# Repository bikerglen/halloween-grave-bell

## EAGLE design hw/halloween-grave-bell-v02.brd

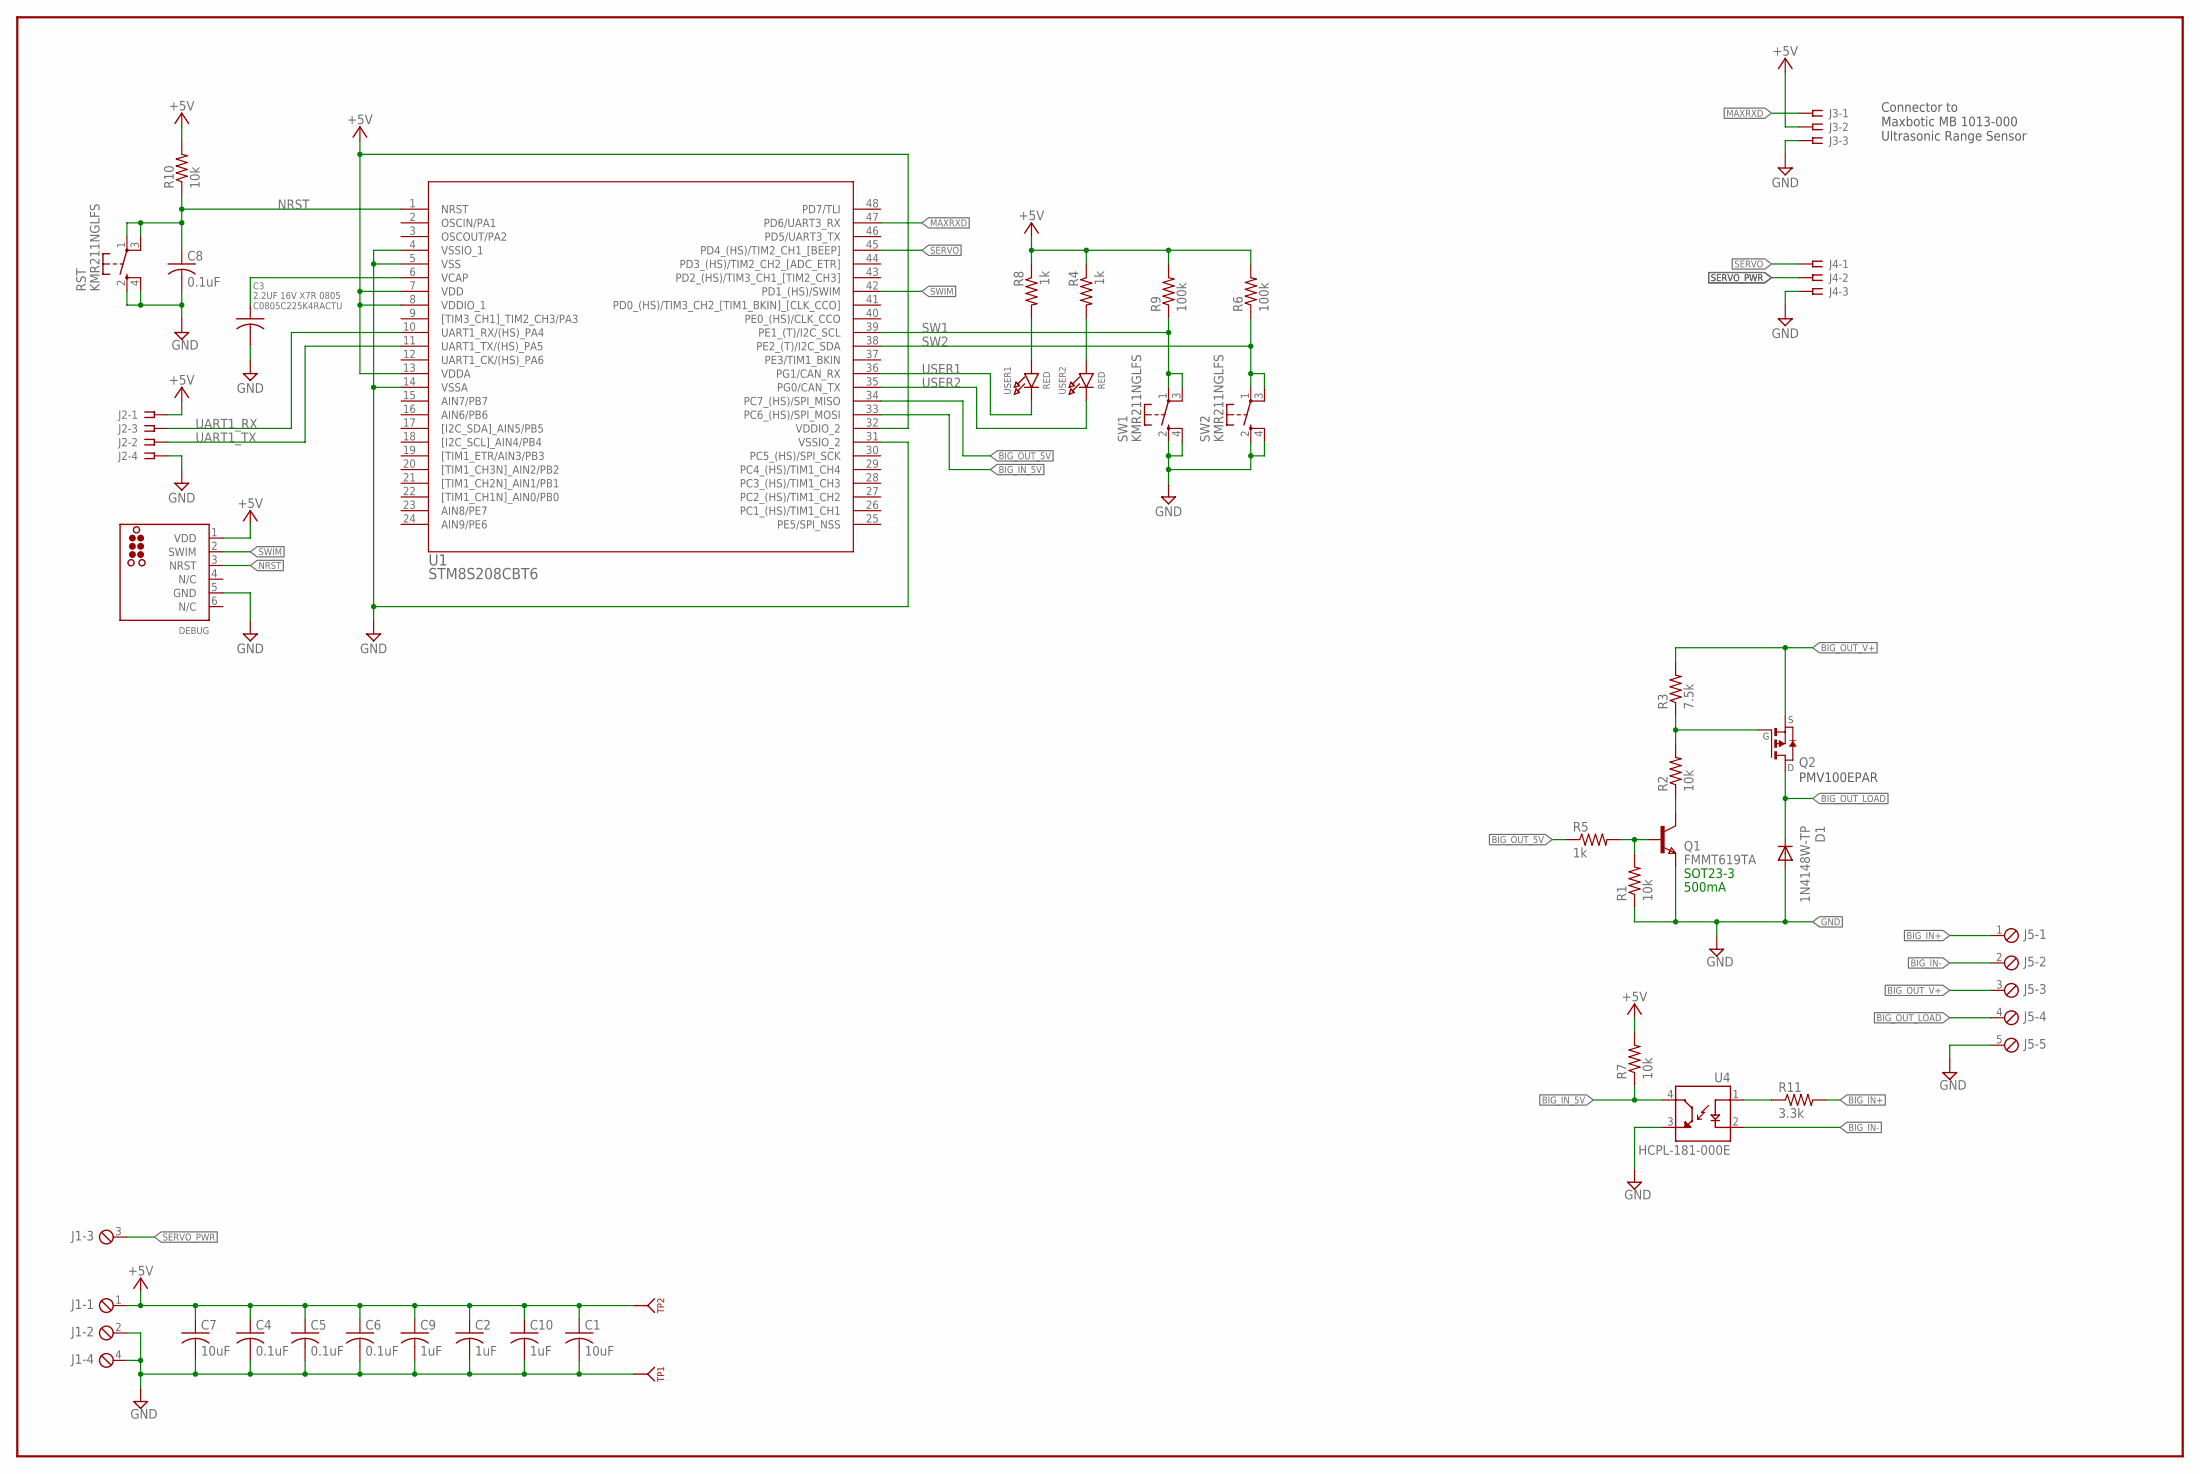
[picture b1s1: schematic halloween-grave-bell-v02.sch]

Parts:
C1, C7: 10uF; C1210; MFR_PART_NO C1210C105K4PACTU
C2, C9, C10: 1uF; C0603
C3: 2.2UF 16V X7R 0805; C0805; MFR_PART_NUM C0805C225K4RACTU
C4, C5, C6: 0.1uF; C0603
C8: 0.1uF; C0805
D1: 1N4148W-TP; SOD123
DEBUG: TC2030-NL-STM8; TC2030-NL
J1: MPT4; 4POL254
J2: SSW-104-02-S-S
J3, J4: SSW-103-02-S-S
J5: MPT5; 5POL254
Q1: FMMT619TA; SOT-23
Q2: PMOSSOT23; SOT-23
R1, R2, R7: 10k; R0603
R3: 7.5k; R0603
R4, R8: 1k; R0805
R5: 1k; R0603
R6, R9: 100k; R0805
R10: 10k; R0805
R11: 3.3k; R0603
RST: KMR211NGLFS; KMR2
SW1, SW2: KMR211NGLFS; KMR2
TP1, TP2: KEYSTONE_500X; KEYSTONE_TP500X
U1: STM8S208CBT6; LQFP-48_STM
U4: HCPL-181-000E; SOIC254P675X240-4N
USER1, USER2: RED; CHIPLED_0805_NOOUTLINE

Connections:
+5V: C1.1, C2.1, C4.1, C5.1, C6.1, C7.1, C9.1, C10.1, DEBUG.1 (VDD), J1.1, J2.1, J3.2, R4.1, R6.2, R7.2, R8.1, R9.2, R10.2, TP2.1, U1.7 (VDD), U1.8 (VDDIO_1), U1.13 (VDDA), U1.32 (VDDIO_2)
BIG_IN+: J5.1, R11.2
BIG_IN-: J5.2, U4.2 (CATHODE)
BIG_IN_5V: R7.1, U1.33 (PC6_(HS)/SPI_MOSI), U4.4 (COLLECTOR)
BIG_OUT_5V: R5.1, U1.34 (PC7_(HS)/SPI_MISO)
BIG_OUT_LOAD: D1.C, J5.4, Q2.1 (D)
BIG_OUT_V+: J5.3, Q2.2 (S), R3.2
GND: C1.2, C2.2, C3.2, C4.2, C5.2, C6.2, C7.2, C8.2, C9.2, C10.2, D1.A, DEBUG.5 (GND), J1.2, J1.4, J2.4, J3.3, J4.3, J5.5, Q1.2 (E), R1.1, RST.2 (S), RST.4 (S1), SW1.2 (S), SW1.4 (S1), SW2.2 (S), SW2.4 (S1), TP1.1, U1.4 (VSSIO_1), U1.5 (VSS), U1.14 (VSSA), U1.31 (VSSIO_2), U4.3 (EMITTER)
MAXRXD: J3.1, U1.47 (PD6/UART3_RX)
unnamed: Q1.1 (C), R2.1
unnamed: R8.2, USER1.A
unnamed: Q2.3 (G), R2.2, R3.1
unnamed: R4.2, USER2.A
unnamed: R11.1, U4.1 (ANODE)
unnamed: Q1.3 (B), R1.2, R5.2
NRST: C8.1, DEBUG.3 (NRST), R10.1, RST.1, RST.3 (P1), U1.1 (NRST)
SERVO: J4.1, U1.45 (PD4_(HS)/TIM2_CH1_[BEEP])
SERVO_PWR: J1.3, J4.2
SW1: R9.1, SW1.1, SW1.3 (P1), U1.39 (PE1_(T)/I2C_SCL)
SW2: R6.1, SW2.1, SW2.3 (P1), U1.38 (PE2_(T)/I2C_SDA)
SWIM: DEBUG.2 (SWIM), U1.42 (PD1_(HS)/SWIM)
UART1_RX: J2.3, U1.10 (UART1_RX/(HS)_PA4)
UART1_TX: J2.2, U1.11 (UART1_TX/(HS)_PA5)
USER1: U1.36 (PG1/CAN_RX), USER1.C
USER2: U1.35 (PG0/CAN_TX), USER2.C
VCAP: C3.1, U1.6 (VCAP)

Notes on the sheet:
SOT23-3
500mA
‎PMV100EPAR‎
Connector to Maxbotic MB 1013-000 Ultrasonic Range Sensor

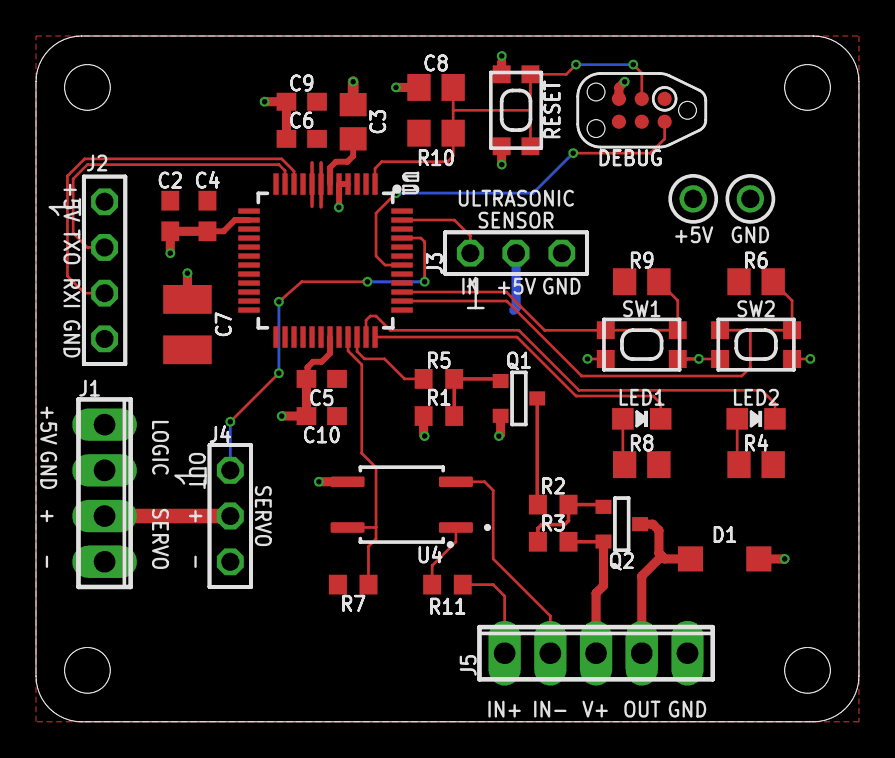
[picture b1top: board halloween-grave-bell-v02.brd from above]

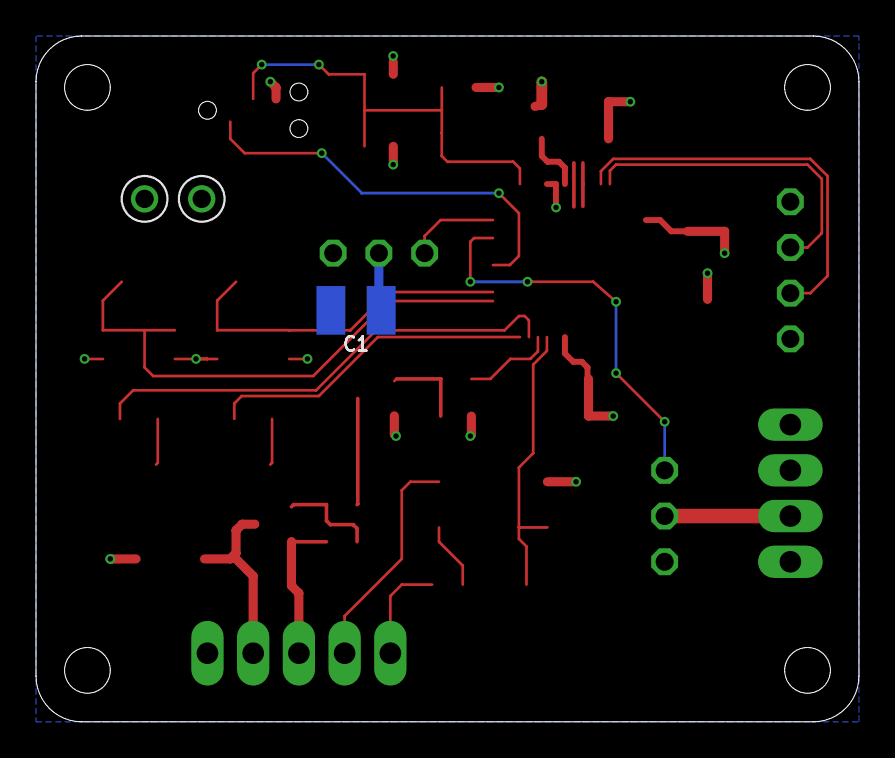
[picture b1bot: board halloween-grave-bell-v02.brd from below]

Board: 2 copper layers, 45.7 x 38.1 mm, 39 parts (3 on the bottom side), 26 nets.

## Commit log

2020-12-24 initial checkin
2020-12-24 added .gitignore
2020-12-24 improved range diagnostics
2020-12-24 added nucleo 64 board connections
2021-01-12 ported from nucleo eval board to real board
2021-09-05 add board design files
2021-09-14 add dxf files for the metal bits

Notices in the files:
parts and their libraries:
microbuilder: This work is placed in the public domain, and may be freely used for commercial and non-commercial work with the following conditions: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
